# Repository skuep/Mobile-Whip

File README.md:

# Mobile-Whip
The Mobile-Whip is an active (receive only) wideband antenna mainly designed for the HF frequency range (100kHz - 30MHz). The design is heavily based on the very famous **Mini-Whip** Antenna by PA0RDT (and DL4ZAO) with the main design change of making it operate on a single cell lithium battery (or USB supply voltage) to be able to use it on a mobile radio. 

This led to the following improvements:

- Operates on a single lithium cell, 5V USB Supply, 4.0V RTL-SDR V4 Bias-Tee or 12V-15V Mini-Whip Bias-Tee
- Includes lithium battery charger
- Uses a LTC6268 ultra-low input capacitance OPAMP instead of JFET input
- Requires only 20mA (instead of roughly 50mA)
- (Probably) Has better large signal interferer resiliency (causing intermodulation) so it might perform better indoors
- Designed for 0.1MHz to 30MHz, but works reasonably well also for listening on FM Radio (100MHz) and VHF bands (150MHz)
- Can be easily mounted on a HT (such as the UV-K5 with HF mod) or mobile scanner and is thus ideally suited for e.g. SHTF Emergency Operations
- Very compact, only 200mm length
- 3D-Printed Enclosure (TBD)

**Important**: This project is currently in it's first revision for preview purposes only. There may (and are) some issues with this design still that need to be addressed in the future.

**Attention**: There is currently no reverse-TX protection, should you mount the Mobile-Whip on a mobile and press the PTT button. The Mobile-Whip might break.

            |  
:-------------------------:|:-------------------------:
Mobile Whip on a UV-K5 with HF-mod | Mobile Whip on a RTL-SDR with Bias-Tee

            |  
:-------------------------:|:-------------------------:
S9+ on UV-K5 | Integrated USB-Charger

## How can I get one?
The PCB can be ordered fully-assembled (apart from SMA male connector and lithium cell holder) at JLCPCB by following these instructions:

- Go to JLCPCB.com and upload the ``GERBER-mobile-whip.zip`` package (under ``kicad/mobile-whip/jlcpcb/production_files``)
  - Select PCB Thickness 1.6mm
  - You may want to select LeadFree HASL
  - Select Silkscreen/Soldermask color to your liking
- Check "PCB Assembly"
  - PCBA Type "Economic"
  - Assembly Side "Top Side"
  - Tooling Holes "Added by Customer"
  - Press Next
  - Click "Add BOM File" and upload ``BOM-mobile-whip.csv``
  - Click "Add CPL File" and upload ``CPL-mobile-whip.csv``
  - Press Next
  - Look Through components, see if something is missing or problematic
  - **Make sure that all listed components are selected** and press Next 
  - Check everything looks roughly good (rotations are already baked-in and should be correct). Save to Cart

**Note**:
The following warning is okay and can be ignored:

*The below parts won't be assembled due to missing data: 
C3, D4, C4, D6, J1, H1, H2, BT1*

This will give you 5 (or more) SMD assembled mobile-whip antennas for roughly 25€ per piece.

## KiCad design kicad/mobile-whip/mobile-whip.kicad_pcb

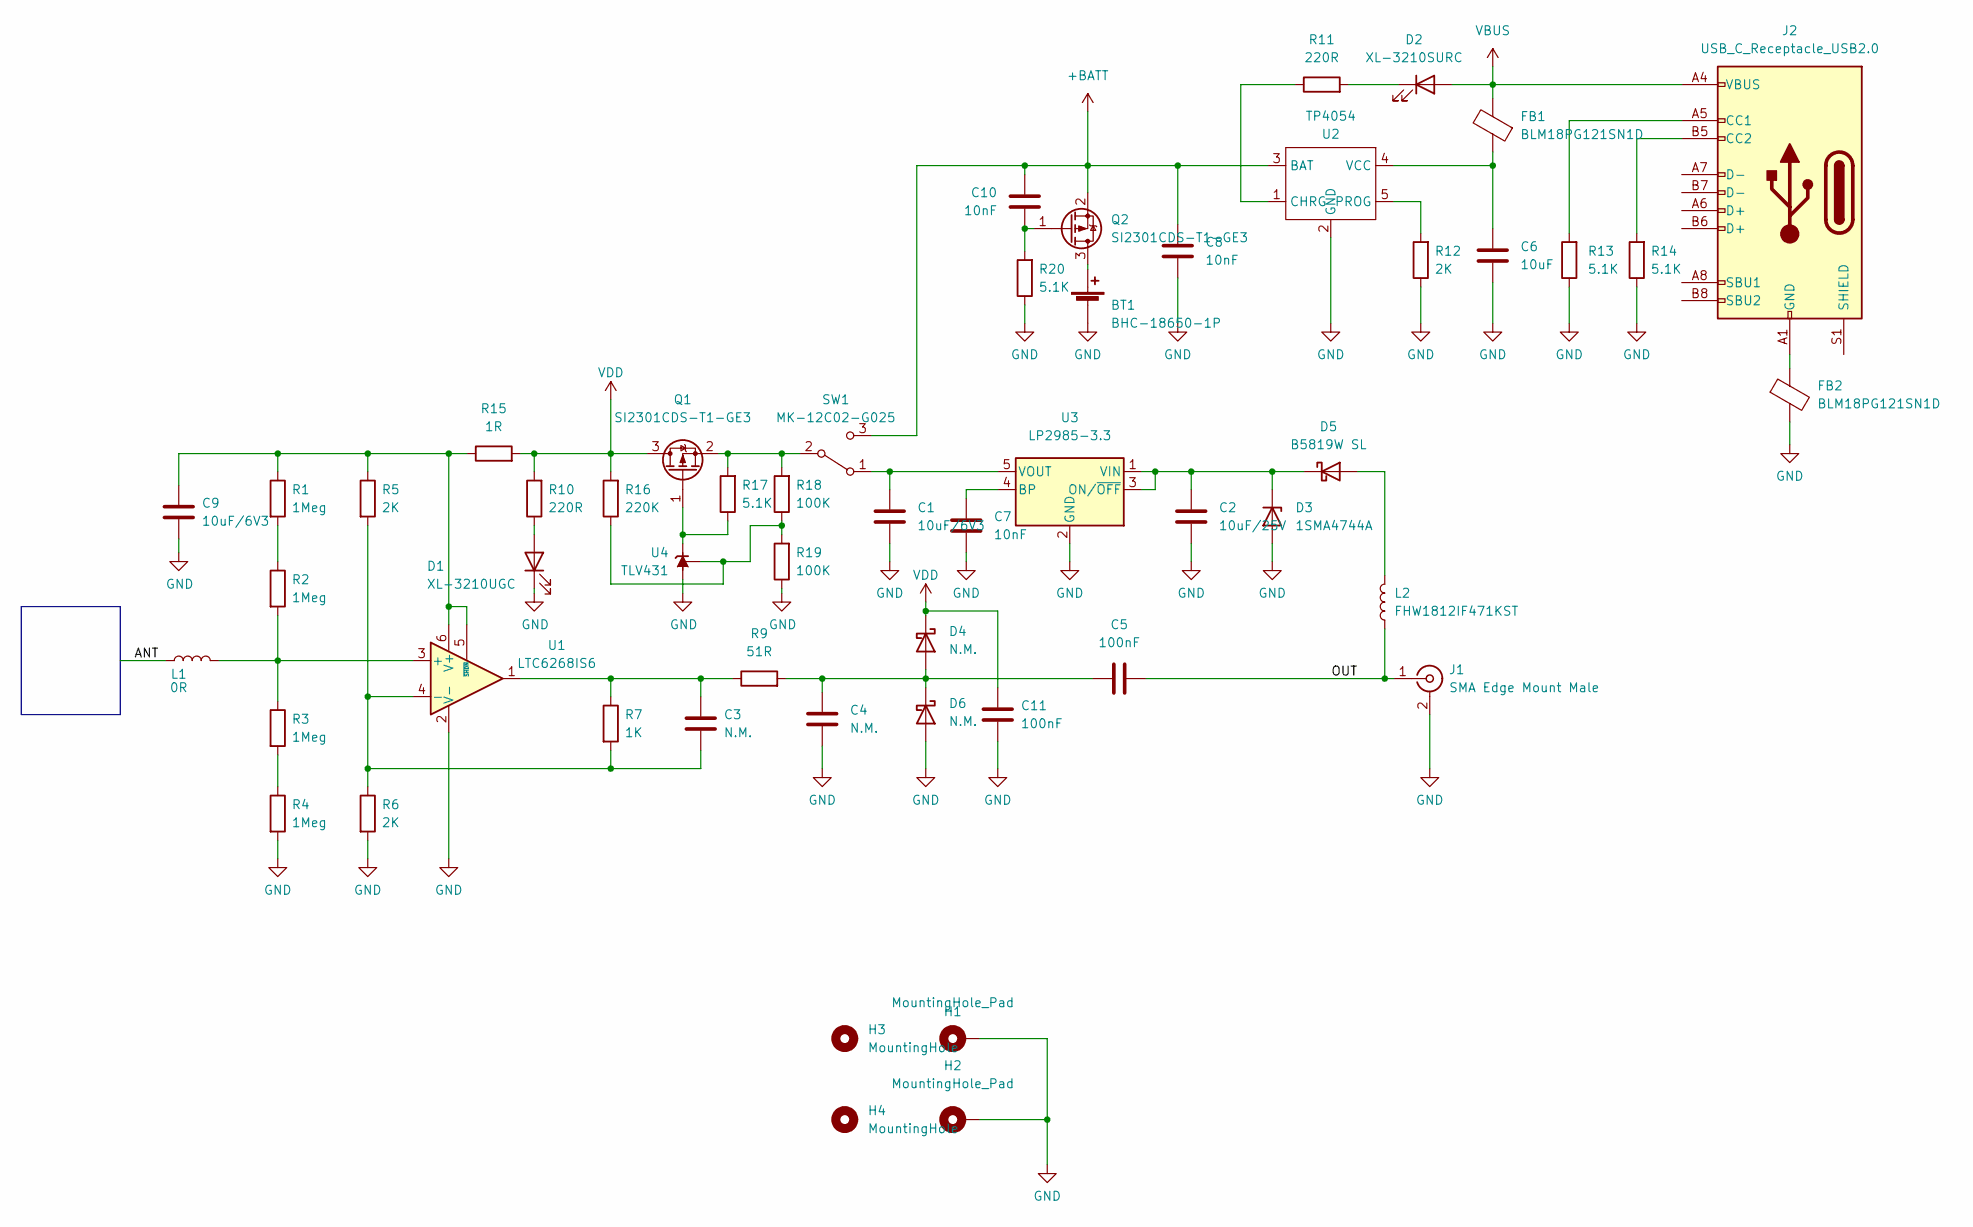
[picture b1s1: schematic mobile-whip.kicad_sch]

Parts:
BT1: BHC-18650-1P
C1, C9: 10uF/6V3; C_0805_2012Metric
C2: 10uF/25V; C_0805_2012Metric
C3, C4: N.M.; C_0805_2012Metric
C5, C11: 100nF; C_0805_2012Metric
C6: 10uF; C_0805_2012Metric
C7, C8, C10: 10nF; C_0805_2012Metric
D1: XL-3210UGC; LED_Side_3.2x1.5
D2: XL-3210SURC; LED_Side_3.2x1.5
D3: 1SMA4744A; D_SMA
D4, D6: N.M.; D_SOD-123
D5: B5819W SL; D_SOD-123
FB1, FB2: BLM18PG121SN1D; L_0603_1608Metric
H1, H2: MountingHole_Pad; MountingHole_3.2mm_M3_ISO7380_Pad_TopBottom
H3, H4: MountingHole; TOOLING-HOLE
J1: SMA Edge Mount Male; SMA_Male_EdgeMount
J2: USB_C_Receptacle_USB2.0; USB_C_Receptacle_GCT_USB4105-xx-A_16P_TopMnt_Horizontal
L1: 0R; L_0805_2012Metric
L2: FHW1812IF471KST; L_1812_4532Metric
Q1, Q2: SI2301CDS-T1-GE3; SOT-23
R1, R2, R3, R4: 1Meg; R_0805_2012Metric
R5, R6, R12: 2K; R_0805_2012Metric
R7: 1K; R_0805_2012Metric
R9: 51R; R_0805_2012Metric
R10, R11: 220R; R_0805_2012Metric
R13, R14, R17, R20: 5.1K; R_0805_2012Metric
R15: 1R; R_0805_2012Metric
R16: 220K; R_0805_2012Metric
R18, R19: 100K; R_0805_2012Metric
SW1: MK-12C02-G025; SW_SPDT_PCM12
U1: LTC6268IS6; TSOT-23-6
U2: TP4054; SOT-23-5
U3: LP2985-3.3; SOT-23-5
U4: TLV431; SOT-23

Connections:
+BATT: C8.2, C10.2, Q2.2 (S), SW1.3 (C), U2.3 (BAT)
/ANT: L1.1
/OUT: C5.2, J1.1 (In), L2.1
GND: BT1.2 (-), C1.2, C2.2, C4.2, C6.2, C7.1, C8.1, C9.2, C11.1, D1.1 (K), D3.2 (A), D6.2 (A), FB2.2, H1.1, H2.1, J1.2 (Ext), R4.2, R6.2, R12.1, R13.1, R14.1, R19.1, R20.1, U1.2 (V-), U2.2 (GND), U3.2 (GND), U4.3 (A)
unnamed: BT1.1 (+), Q2.3 (D)
unnamed: C1.1, SW1.1 (A), U3.5 (VOUT)
unnamed: C2.1, D3.1 (K), D5.1 (K), U3.1 (VIN), U3.3 (ON/~OFF)
unnamed: C3.1, R7.1, R9.1, U1.1
unnamed: C3.2, R5.2, R6.1, R7.2, U1.4 (-)
unnamed: C4.1, C5.1, D4.2 (A), D6.1 (K), R9.2
unnamed: C6.1, FB1.1, U2.4 (VCC)
unnamed: C7.2, U3.4 (BP)
unnamed: C9.1, R1.1, R5.1, R15.1, U1.5 (~SHDN), U1.6 (V+)
unnamed: C10.1, Q2.1 (G), R20.2
unnamed: D1.2 (A), R10.1
unnamed: D2.1 (K), R11.2
unnamed: D5.2 (A), L2.2
unnamed: FB2.1, J2.A1 (GND), J2.A12 (GND), J2.B1 (GND), J2.B12 (GND)
unnamed: J2.A5 (CC1), R13.2
unnamed: J2.B5 (CC2), R14.2
unnamed: L1.2, R2.2, R3.1, U1.3 (+)
unnamed: Q1.1 (G), R17.1, U4.1 (K)
unnamed: Q1.2 (S), R17.2, R18.2, SW1.2 (B)
unnamed: R1.2, R2.1
unnamed: R3.2, R4.1
unnamed: R11.1, U2.1 (CHRG)
unnamed: R12.2, U2.5 (PROG)
unnamed: R16.1, R18.1, R19.2, U4.2 (REF)
VBUS: D2.2 (A), FB1.2, J2.A4 (VBUS), J2.A9 (VBUS), J2.B4 (VBUS), J2.B9 (VBUS)
VDD: C11.2, D4.1 (K), Q1.3 (D), R10.2, R15.2, R16.2

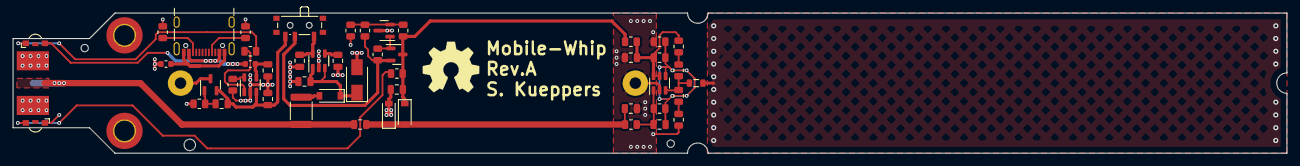
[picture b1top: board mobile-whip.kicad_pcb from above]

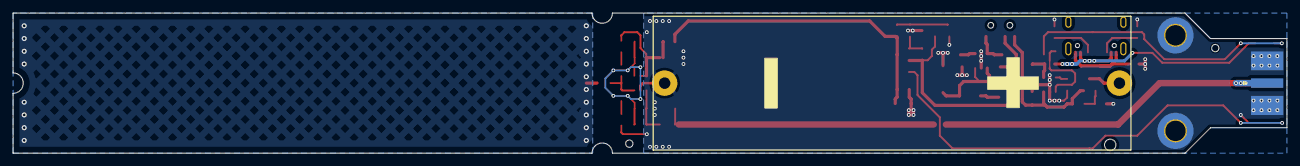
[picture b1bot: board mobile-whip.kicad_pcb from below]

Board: 2 copper layers, 200.0 x 22.0 mm, 54 parts (2 on the bottom side), 29 nets.

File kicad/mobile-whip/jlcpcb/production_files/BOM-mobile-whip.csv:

Comment,Designator,Footprint,LCSC
SI2301CDS-T1-GE3,"Q1,Q2",SOT-23,C10487
MK-12C02-G025,SW1,SW_SPDT_PCM12,C136659
BLM18PG121SN1D,"FB1,FB2",L_0603_1608Metric,C14709
100K,"R18,R19",R_0805_2012Metric,C149504
10uF/6V3,"C1,C2,C6,C9",C_0805_2012Metric,C15850
10nF,"C10,C7,C8",C_0805_2012Metric,C1710
0R,L1,L_0805_2012Metric,C17477
1K,R7,R_0805_2012Metric,C17513
1Meg,"R1,R2,R3,R4",R_0805_2012Metric,C17514
220K,R16,R_0805_2012Metric,C17556
220R,"R10,R11",R_0805_2012Metric,C17557
2K,"R12,R5,R6",R_0805_2012Metric,C17604
51R,R9,R_0805_2012Metric,C17738
1SMA4744A,D3,D_SMA,C19077482
1R,R15,R_0805_2012Metric,C25271
5.1K,"R13,R14,R17,R20",R_0805_2012Metric,C27834
100nF,"C11,C5",C_0805_2012Metric,C28233
USB_C_Receptacle_USB2.0,J2,USB_C_Receptacle_GCT_USB4105-xx-A_16P_TopMnt_Horizontal,C2988369
FHW1812IF471KST,L2,L_1812_4532Metric,C394141
TLV431,U4,SOT-23,C56765
TP4054,U2,SOT-23-5,C668215
LTC6268IS6,U1,TSOT-23-6,C689166
B5819W SL,D5,D_SOD-123,C8598
LP2985-3.3,U3,SOT-23-5,C95414
XL-3210SURC,D2,LED_Side_3.2x1.5,C965874
XL-3210UGC,D1,LED_Side_3.2x1.5,C965877
N.M.,C3,C_0805_2012Metric,
N.M.,C4,C_0805_2012Metric,
MountingHole_Pad,H1,MountingHole_3.2mm_M3_ISO7380_Pad_TopBottom,
MountingHole_Pad,H2,MountingHole_3.2mm_M3_ISO7380_Pad_TopBottom,
SMA Edge Mount Male,J1,SMA_Male_EdgeMount,
BHC-18650-1P,BT1,BHC-18650-1P,
MountingHole,H4,TOOLING-HOLE,
MountingHole,H3,TOOLING-HOLE,
N.M.,D6,D_SOD-123,
N.M.,D4,D_SOD-123,

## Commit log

2025-11-22 Add simulation of battery protection
2025-11-22 Finalize design
2025-11-22 Add thermals
2025-11-22 Added LCSC part numbers
2025-11-22 Add JLCPCB production files
2025-11-22 Fix rotations
2025-11-22 Fix LED footprint
2025-11-22 Add tooling holes
2025-11-22 Added component value to SMA connector
2025-11-22 Use 100nF AC coupling cap
2025-11-22 Changed some resistor values
2025-11-22 Update simulation values
2025-11-22 Choose OSHW symbol only
2025-11-23 Final touches
2025-11-23 Move SMA edge mount further to the edge
2025-11-29 Add images
2025-11-29 Adjust lithium cell footprint and change red LED resistor to 220R
2025-11-29 Add schematic pdf
2025-12-07 Add JLCPCB instructions
2025-12-07 Add CERN OHL license
2025-12-16 Remove lowpass capacitors and short input inductor
2026-01-01 Update schematic
